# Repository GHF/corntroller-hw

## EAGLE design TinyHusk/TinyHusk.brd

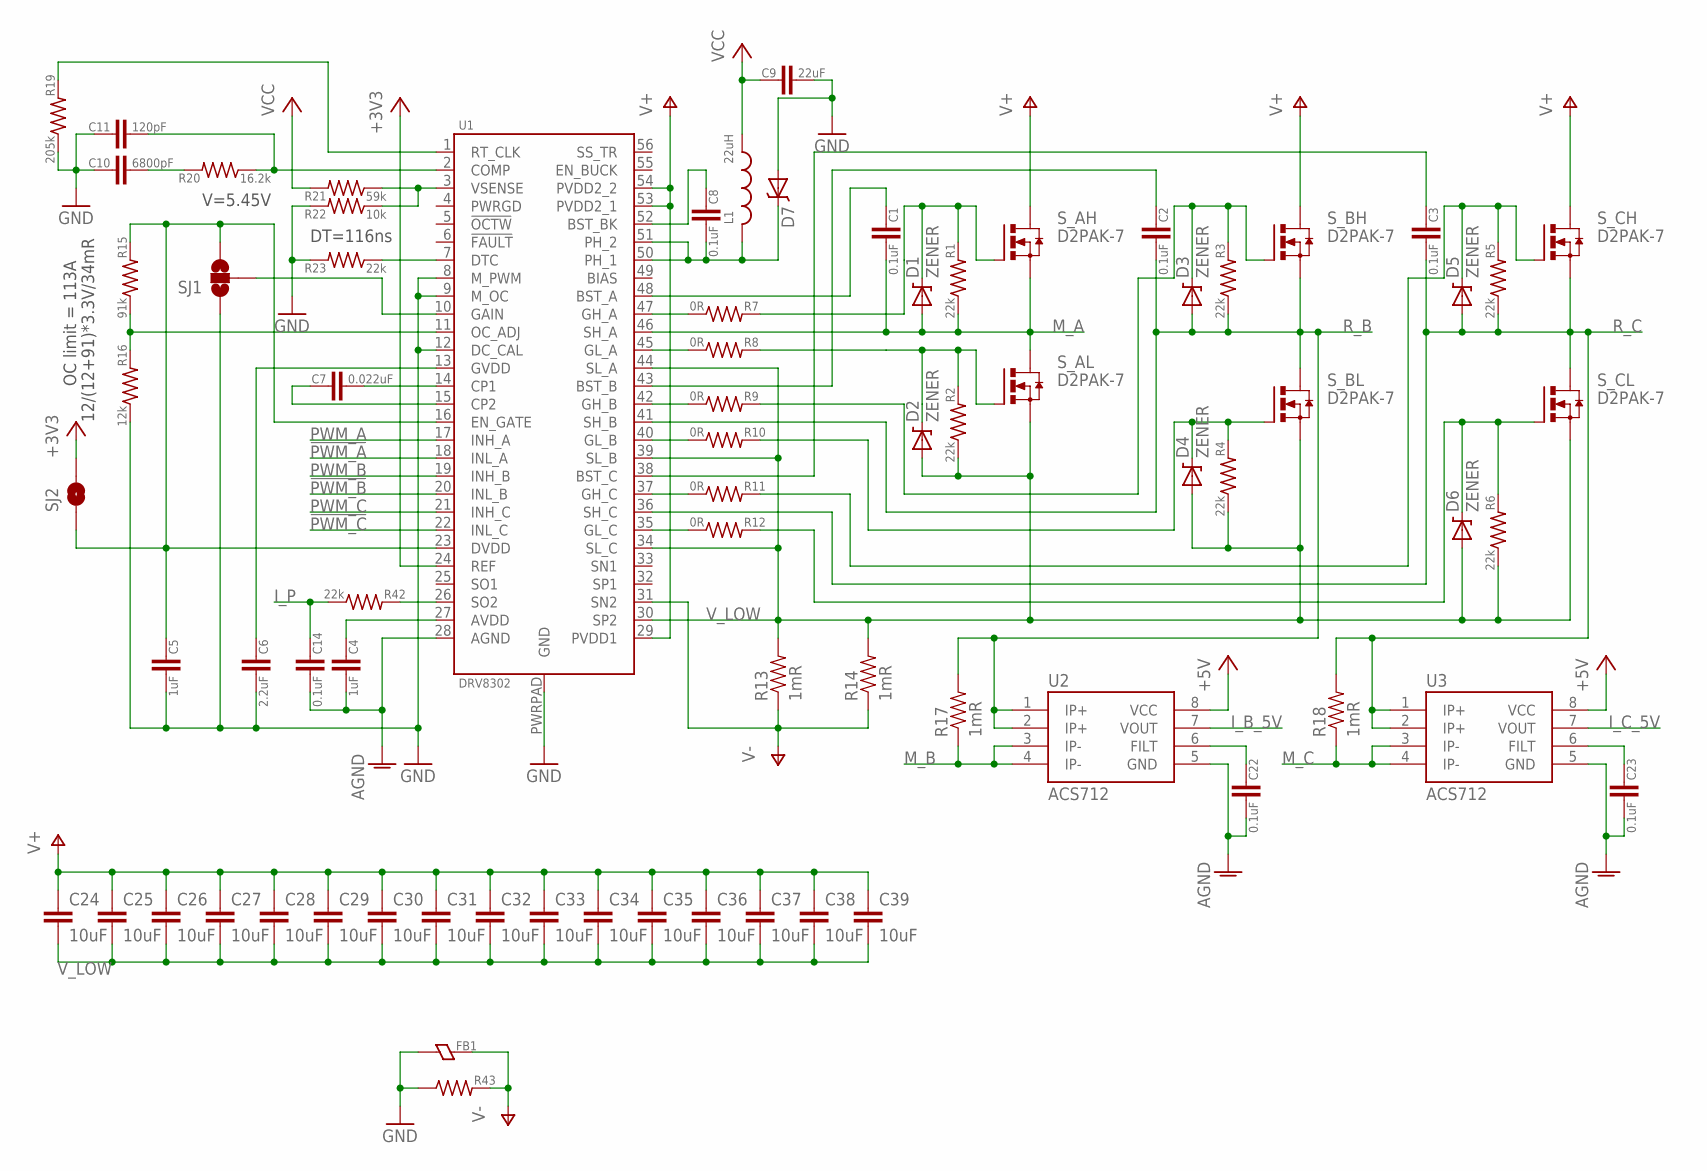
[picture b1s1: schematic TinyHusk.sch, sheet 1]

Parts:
C1, C2, C3, C8, C14, C22, C23: 0.1uF; 0603
C4, C5: 1uF; 0603
C6: 2.2uF; 0603
C7: 0.022uF; 0603
C9: 22uF; 0805
C10: 6800pF; 0603
C11: 120pF; 0603
C24, C25, C26, C27, C28, C29, C30, C31, C32, C33, C34, C35, C36, C37, C38, C39: 10uF; 1210
D1, D2, D3, D4, D5, D6: ZENER; SOD-323
D7: DIODE-SCHOTTKY_; SMA-DIODE
FB1: FERRITE0603; 0603
L1: 22uH; TAIYO-YUDEN_NR50
R1, R2, R3, R4, R5, R6, R23, R42: 22k; 0603
R7, R8, R9, R10, R11, R12: 0R; 0603
R13, R14, R17, R18: 1mR; R2512
R15: 91k; 0603
R16: 12k; 0603
R19: 205k; 0603
R20: 16.2k; 0603
R21: 59k; 0603
R22: 10k; 0603
R43: R0603; 0603
SJ1: SOLDERJUMPER_2WAYS; SJ_X
SJ2: SOLDERJUMPERTRACE; SJ_2S-TRACE
S_AH: D2PAK-7
S_AL: D2PAK-7
S_BH: D2PAK-7
S_BL: D2PAK-7
S_CH: D2PAK-7
S_CL: D2PAK-7
U1: DRV8302; HTSSOP-56
U2, U3: ACS712; SO08

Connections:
!PWM_A: U1.18 (INL_A); also elsewhere on the board
!PWM_B: U1.20 (INL_B); also elsewhere on the board
!PWM_C: U1.22 (INL_C); also elsewhere on the board
+3V3: SJ2.2, U1.24 (REF); also elsewhere on the board
+5V: U2.8 (VCC), U3.8 (VCC); also elsewhere on the board
AGND: C4.2, C14.2, C22.2, C23.2, U1.28 (AGND), U2.5 (GND), U3.5 (GND); also elsewhere on the board
GND: C5.2, C6.2, C9.2, C10.1, C11.1, D7.A, FB1.1, R16.1, R19.1, R22.2, R23.2, R43.1, SJ1.1, U1.8 (M_PWM), U1.9 (M_OC), U1.12 (DC_CAL), U1.PWRPAD (GND); also elsewhere on the board
I_B_5V: U2.7 (VOUT); also elsewhere on the board
I_C_5V: U3.7 (VOUT); also elsewhere on the board
I_P: C14.1, R42.1; also elsewhere on the board
M_A: C1.2, D1.2 (A), R1.1, S_AH.2 (S), S_AH.3 (S), S_AH.5 (S), S_AH.6 (S), S_AH.7 (S), S_AL.4 (D), U1.46 (SH_A); also elsewhere on the board
M_B: R17.1, U2.3 (IP-), U2.4 (IP-)
M_C: R18.1, U3.3 (IP-), U3.4 (IP-)
unnamed: R7.1, U1.47 (GH_A)
unnamed: R8.1, U1.45 (GL_A)
unnamed: R42.2, U1.26 (SO2)
unnamed: D1.1 (C), R1.2, R7.2, S_AH.1 (G)
unnamed: D3.1 (C), R3.2, R9.2, S_BH.1 (G)
unnamed: C22.1, U2.6 (FILT)
unnamed: D4.1 (C), R4.2, R10.2, S_BL.1 (G)
unnamed: R21.1, R22.1, U1.3 (VSENSE)
unnamed: D5.1 (C), R5.2, R11.2, S_CH.1 (G)
unnamed: C23.1, U3.6 (FILT)
unnamed: D6.1 (C), R6.2, R12.2, S_CL.1 (G)
unnamed: R9.1, U1.42 (GH_B)
unnamed: C1.1, U1.48 (BST_A)
unnamed: C2.1, U1.43 (BST_B)
unnamed: C3.1, U1.38 (BST_C)
unnamed: R10.1, U1.40 (GL_B)
unnamed: R11.1, U1.37 (GH_C)
unnamed: D2.1 (C), R2.2, R8.2, S_AL.1 (G)
unnamed: R12.1, U1.35 (GL_C)
unnamed: SJ1.2, U1.10 (GAIN)
unnamed: C5.1, R15.2, SJ1.3, SJ2.1, U1.16 (EN_GATE), U1.23 (DVDD)
unnamed: C4.1, U1.27 (AVDD)
unnamed: C6.1, U1.13 (GVDD)
unnamed: C7.2, U1.14 (CP1)
unnamed: C7.1, U1.15 (CP2)
unnamed: R15.1, R16.2, U1.11 (OC_ADJ)
unnamed: C8.2, D7.C, L1.P$2 (2), U1.50 (PH_1), U1.51 (PH_2)
unnamed: C8.1, U1.52 (BST_BK)
unnamed: C11.2, R20.1, U1.2 (COMP)
unnamed: C10.2, R20.2
unnamed: R19.2, U1.1 (RT_CLK)
unnamed: R23.1, U1.7 (DTC)
PWM_A: U1.17 (INH_A); also elsewhere on the board
PWM_B: U1.19 (INH_B); also elsewhere on the board
PWM_C: U1.21 (INH_C); also elsewhere on the board
R_B: C2.2, D3.2 (A), R3.1, R17.2, S_BH.2 (S), S_BH.3 (S), S_BH.5 (S), S_BH.6 (S), S_BH.7 (S), S_BL.4 (D), U1.41 (SH_B), U2.1 (IP+), U2.2 (IP+); also elsewhere on the board
R_C: C3.2, D5.2 (A), R5.1, R18.2, S_CH.2 (S), S_CH.3 (S), S_CH.5 (S), S_CH.6 (S), S_CH.7 (S), S_CL.4 (D), U1.36 (SH_C), U3.1 (IP+), U3.2 (IP+); also elsewhere on the board
V+: C24.1, C25.1, C26.1, C27.1, C28.1, C29.1, C30.1, C31.1, C32.1, C33.1, C34.1, C35.1, C36.1, C37.1, C38.1, C39.1, S_AH.4 (D), S_BH.4 (D), S_CH.4 (D), U1.29 (PVDD1), U1.53 (PVDD2_1), U1.54 (PVDD2_2); also elsewhere on the board
V-: FB1.2, R13.1, R14.1, R43.2, U1.31 (SN2); also elsewhere on the board
VCC: C9.1, L1.P$1 (1), R21.2; also elsewhere on the board
V_LOW: C24.2, C25.2, C26.2, C27.2, C28.2, C29.2, C30.2, C31.2, C32.2, C33.2, C34.2, C35.2, C36.2, C37.2, C38.2, C39.2, D2.2 (A), D4.2 (A), D6.2 (A), R2.1, R4.1, R6.1, R13.2, R14.2, S_AL.2 (S), S_AL.3 (S), S_AL.5 (S), S_AL.6 (S), S_AL.7 (S), S_BL.2 (S), S_BL.3 (S), S_BL.5 (S), S_BL.6 (S), S_BL.7 (S), S_CL.2 (S), S_CL.3 (S), S_CL.5 (S), S_CL.6 (S), S_CL.7 (S), U1.30 (SP2), U1.34 (SL_C), U1.39 (SL_B), U1.44 (SL_A)

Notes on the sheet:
OC limit = 113A
12/(12+91)*3.3V/34mR
V=5.45V
DT=116ns

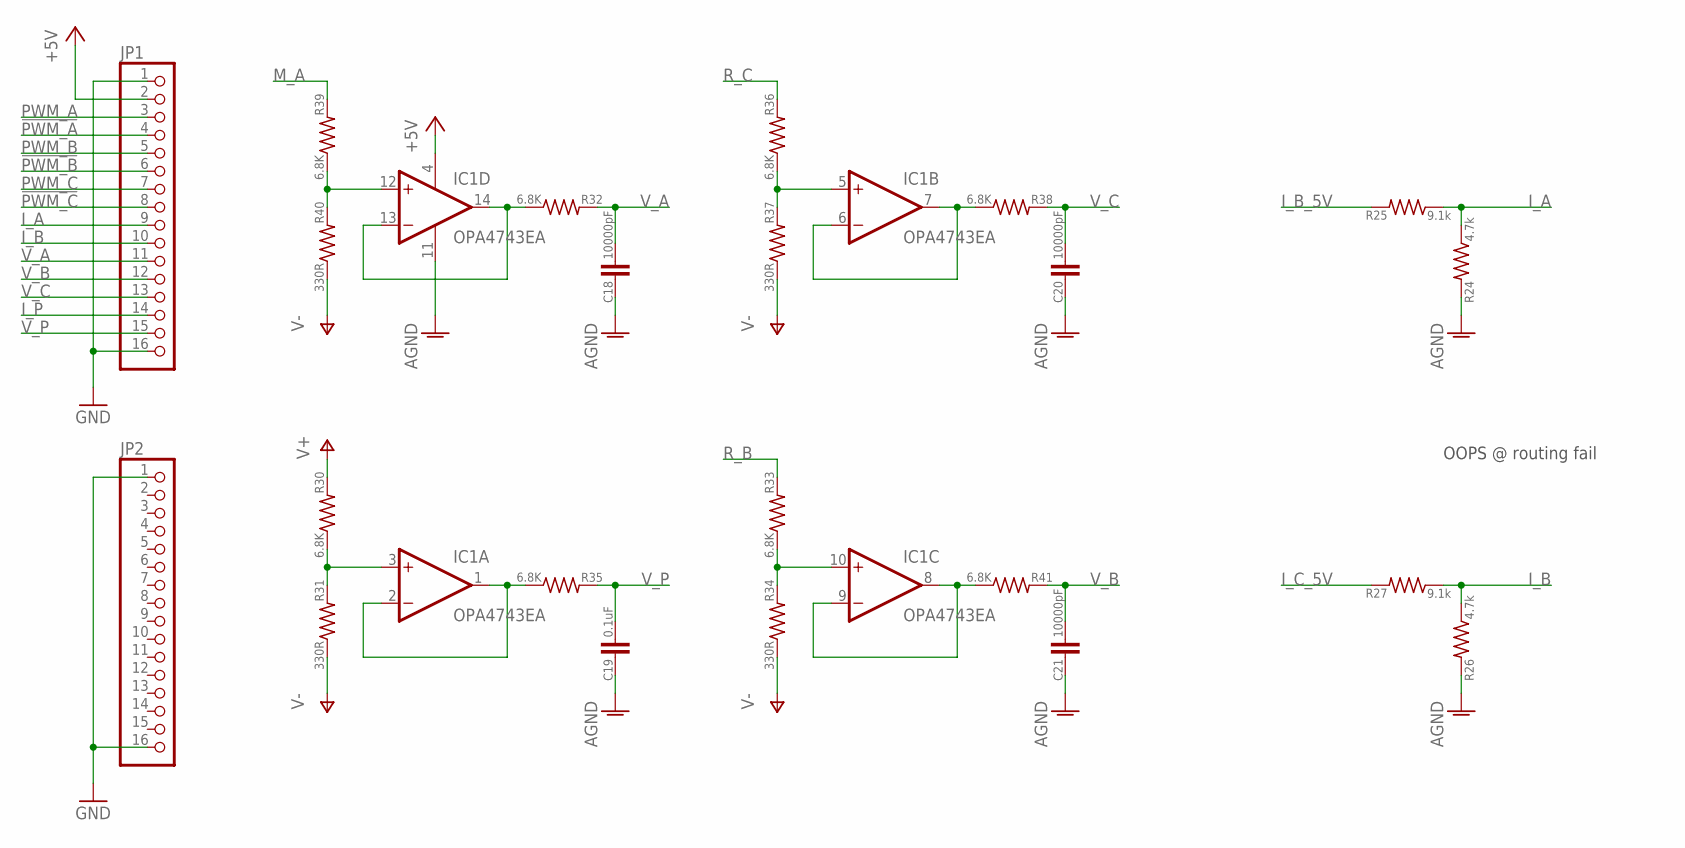
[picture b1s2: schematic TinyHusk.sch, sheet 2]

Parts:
C18, C20, C21: 10000pF; 0603
C19: 0.1uF; 0603
IC1: OPA4743EA; TSSOP14
JP1, JP2: PINHD-1X16_2.54-S; 1X16-S
R24, R26: 4.7k; 0603
R25, R27: 9.1k; 0603
R30, R32, R33, R35, R36, R38, R39, R41: 6.8K; 0603
R31, R34, R37, R40: 330R; 0603

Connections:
!PWM_A: JP1.4; also elsewhere on the board
!PWM_B: JP1.6; also elsewhere on the board
!PWM_C: JP1.8; also elsewhere on the board
+5V: IC1.4 (V+), JP1.2; also elsewhere on the board
AGND: C18.1, C19.1, C20.1, C21.1, IC1.11 (V-), R24.2, R26.2; also elsewhere on the board
GND: JP1.1, JP1.16, JP2.1, JP2.16; also elsewhere on the board
I_A: JP1.9, R24.1, R25.1
I_B: JP1.10, R26.1, R27.1
I_B_5V: R25.2; also elsewhere on the board
I_C_5V: R27.2; also elsewhere on the board
I_P: JP1.14; also elsewhere on the board
M_A: R39.2; also elsewhere on the board
unnamed: IC1.1 (OUT), IC1.2 (-IN), R35.1
unnamed: IC1.6 (-IN), IC1.7 (OUT), R38.1
unnamed: IC1.8 (OUT), IC1.9 (-IN), R41.1
unnamed: IC1.13 (-IN), IC1.14 (OUT), R32.1
unnamed: IC1.3 (+IN), R30.1, R31.2
unnamed: IC1.10 (+IN), R33.1, R34.2
unnamed: IC1.5 (+IN), R36.1, R37.2
unnamed: IC1.12 (+IN), R39.1, R40.2
PWM_A: JP1.3; also elsewhere on the board
PWM_B: JP1.5; also elsewhere on the board
PWM_C: JP1.7; also elsewhere on the board
R_B: R33.2; also elsewhere on the board
R_C: R36.2; also elsewhere on the board
V+: R30.2; also elsewhere on the board
V-: R31.1, R34.1, R37.1, R40.1; also elsewhere on the board
V_A: C18.2, JP1.11, R32.2
V_B: C21.2, JP1.12, R41.2
V_C: C20.2, JP1.13, R38.2
V_P: C19.2, JP1.15, R35.2

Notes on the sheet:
OOPS @ routing fail

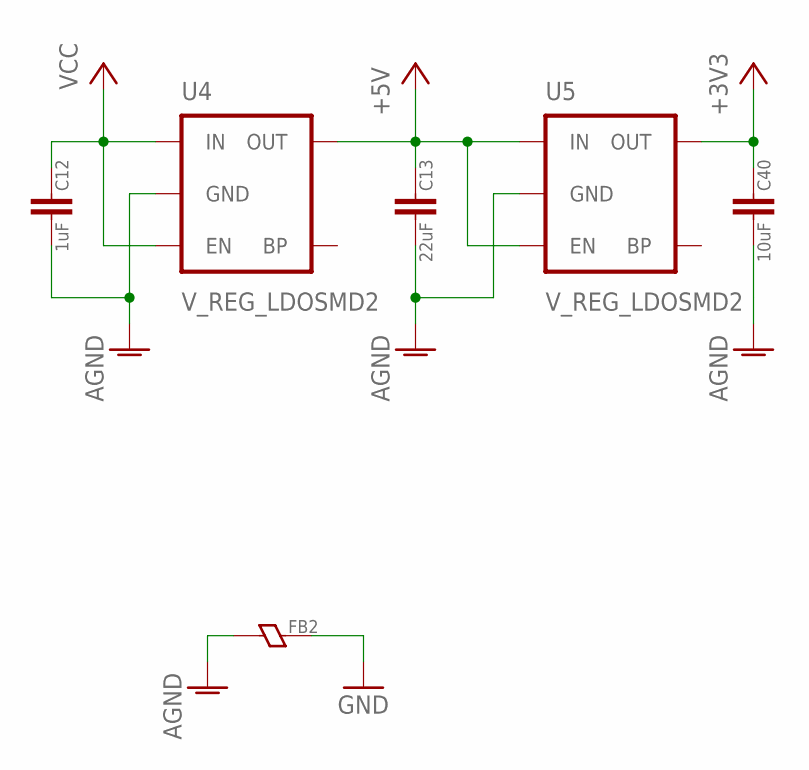
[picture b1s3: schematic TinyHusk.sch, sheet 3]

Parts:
C12: 1uF; 0603
C13: 22uF; 0805
C40: 10uF; 0603
FB2: FERRITE0603; 0603
U4, U5: V_REG_LDOSMD2; SC70

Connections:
+3V3: C40.1, U5.5 (OUT); also elsewhere on the board
+5V: C13.1, U4.5 (OUT), U5.1 (IN), U5.3 (EN); also elsewhere on the board
AGND: C12.2, C13.2, C40.2, FB2.1, U4.2 (GND), U5.2 (GND); also elsewhere on the board
GND: FB2.2; also elsewhere on the board
VCC: C12.1, U4.1 (IN), U4.3 (EN); also elsewhere on the board

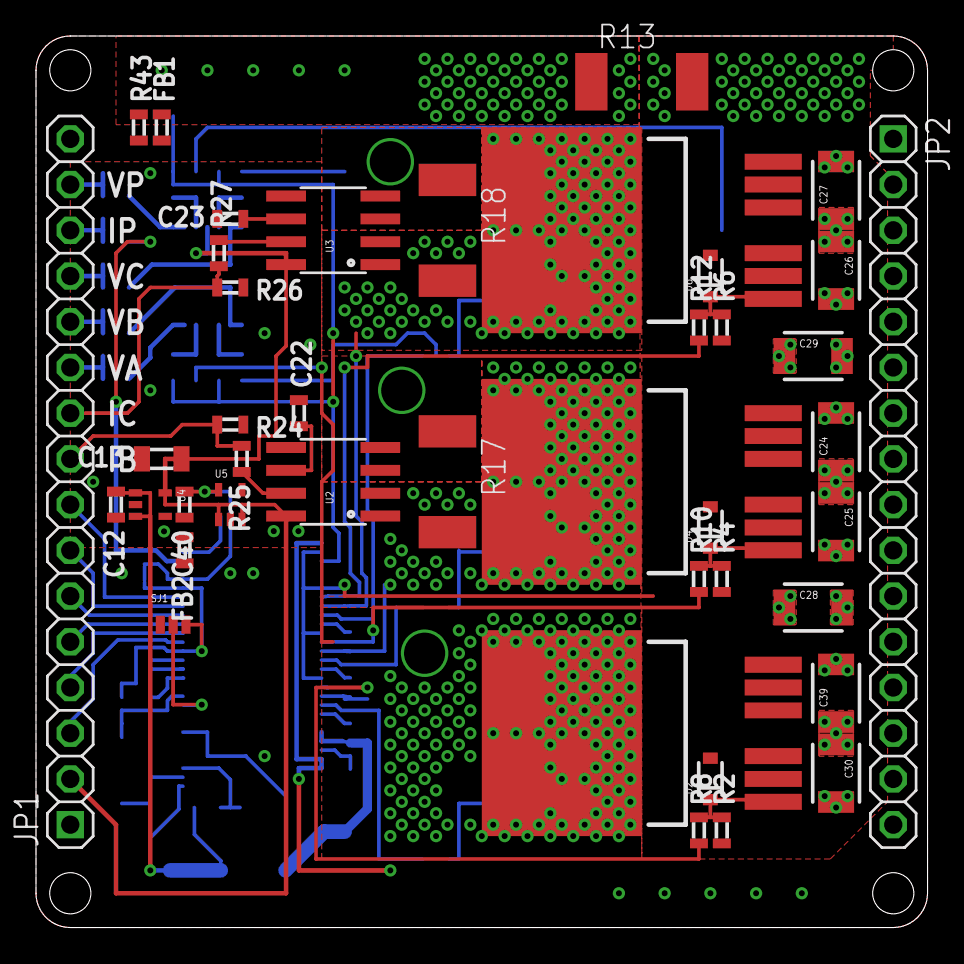
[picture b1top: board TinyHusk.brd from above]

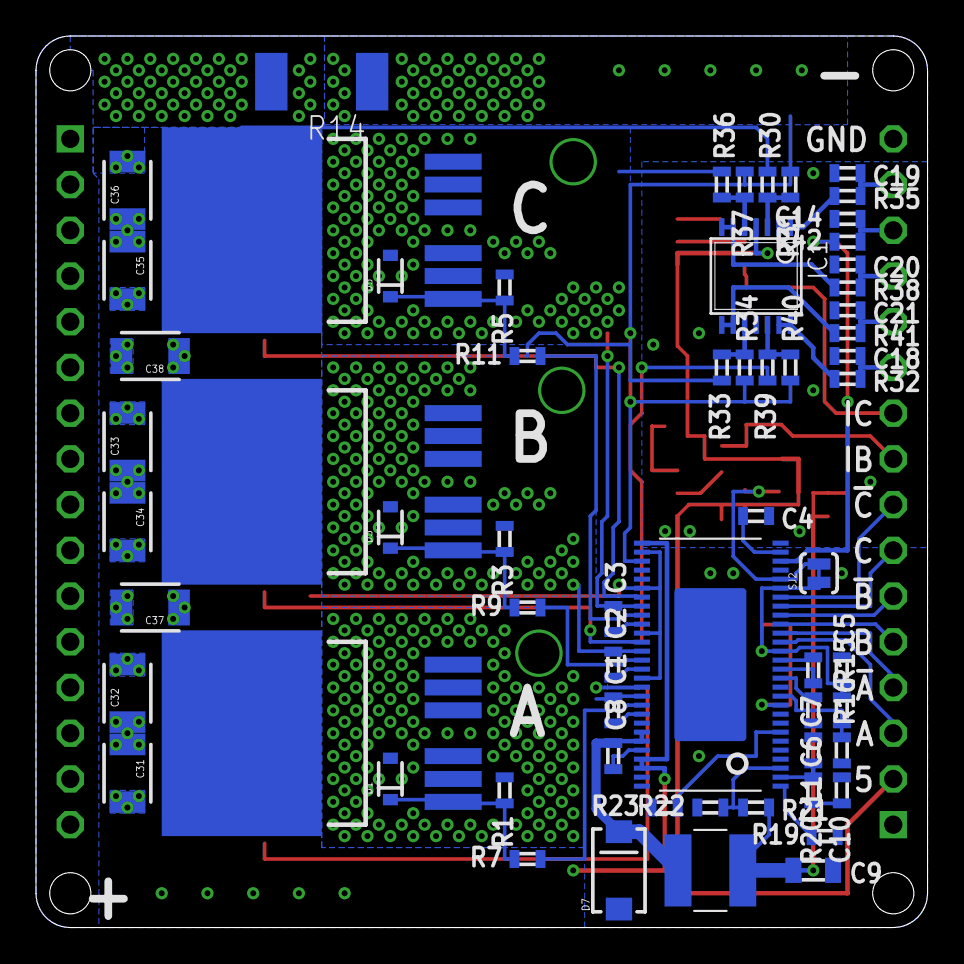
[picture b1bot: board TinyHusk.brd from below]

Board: 2 copper layers, 49.5 x 49.5 mm, 104 parts (62 on the bottom side), 68 nets.

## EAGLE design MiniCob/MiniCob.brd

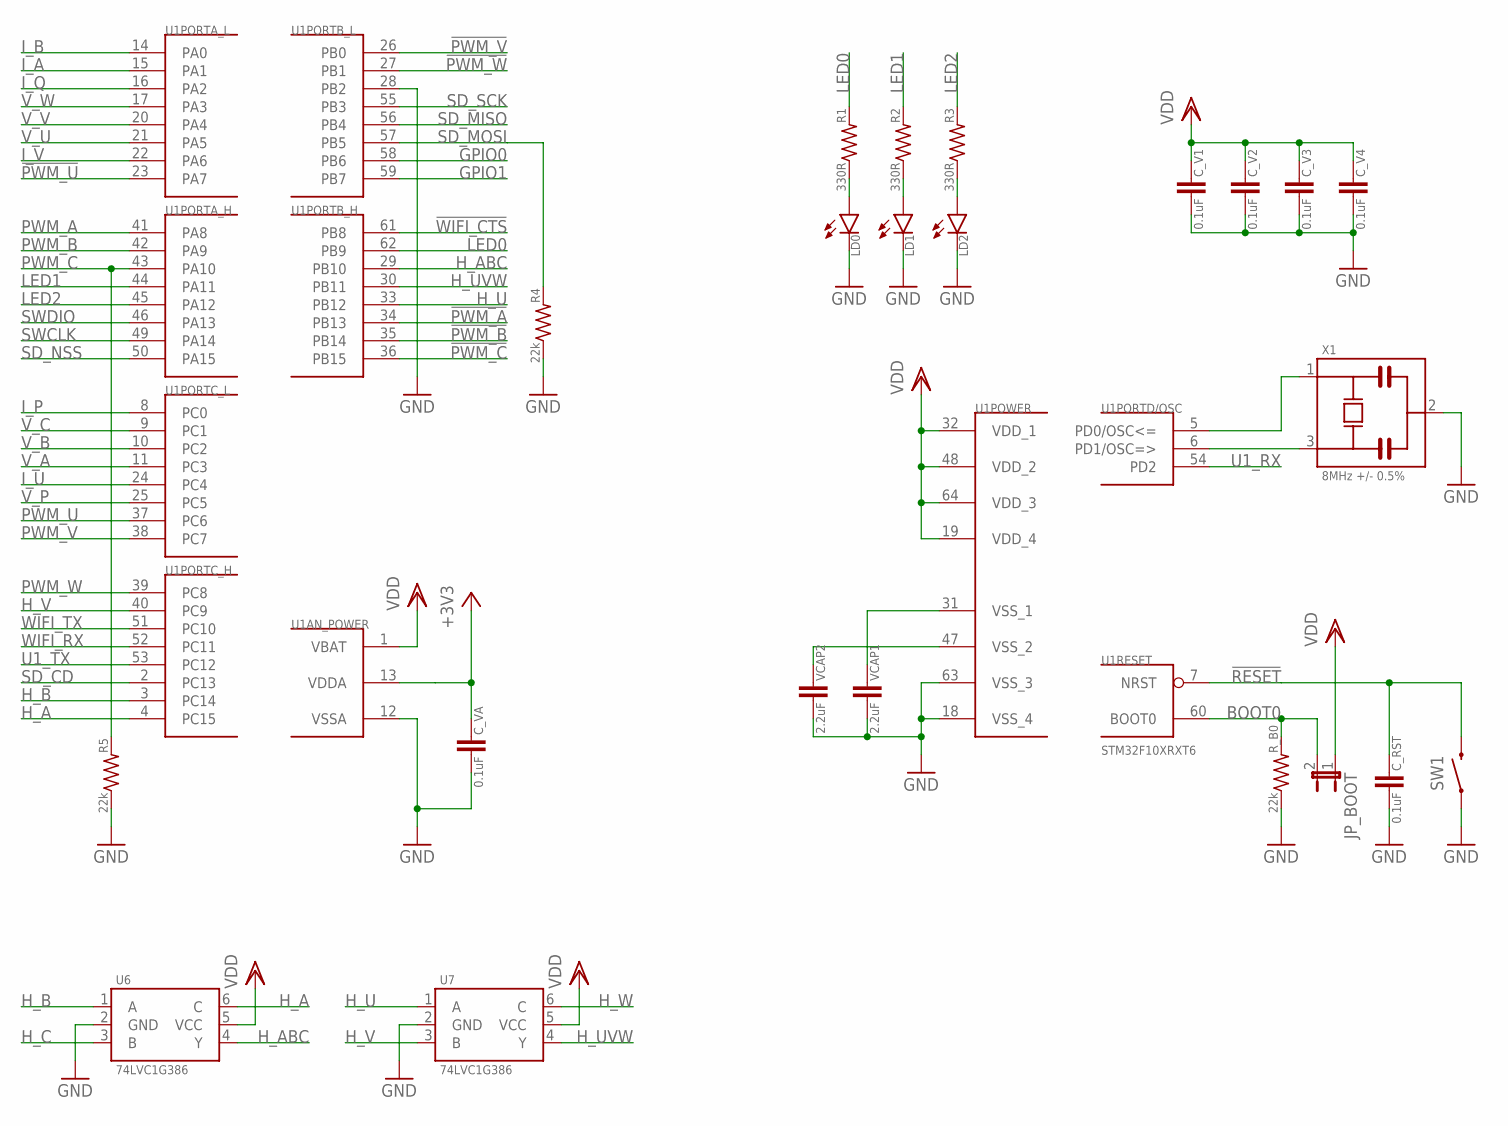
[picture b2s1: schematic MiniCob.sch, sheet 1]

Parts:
C_RST: 0.1uF; 0603
C_V1, C_V2, C_V3, C_V4: 0.1uF; 0603
C_VA: 0.1uF; 0603
JP_BOOT: JUMPER-2PTH; 1X02
LD0, LD1, LD2: LED0805; 0805_POL
R1, R2, R3: 330R; 0603
R4, R5: 22k; 0603
R_B0: 22k; 0603
SW1: SWITCH_SPST-NO; B3U-1000P
U1: STM32F10XRXT6; TQFP64
U6, U7: 74LVC1G386; SC-70
VCAP1, VCAP2: 2.2uF; 0603
X1: 8MHz +/- 0.5%; MURATA_CSTCE

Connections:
!PWM_A: U1.34 (PB13); also elsewhere on the board
!PWM_B: U1.35 (PB14); also elsewhere on the board
!PWM_C: U1.36 (PB15); also elsewhere on the board
!PWM_U: U1.23 (PA7); also elsewhere on the board
!PWM_V: U1.26 (PB0); also elsewhere on the board
!PWM_W: U1.27 (PB1); also elsewhere on the board
!RESET: C_RST.1, SW1.2, U1.7 (NRST); also elsewhere on the board
!WIFI_CTS: U1.61 (PB8); also elsewhere on the board
+3V3: C_VA.1, U1.13 (VDDA); also elsewhere on the board
BOOT0: JP_BOOT.2, R_B0.2, U1.60 (BOOT0)
GND: C_RST.2, C_V1.2, C_V2.2, C_V3.2, C_V4.2, C_VA.2, LD0.- (C), LD1.- (C), LD2.- (C), R4.1, R5.1, R_B0.1, SW1.1, U1.12 (VSSA), U1.18 (VSS_4), U1.28 (PB2), U1.63 (VSS_3), U6.2 (GND), U7.2 (GND), VCAP1.2, VCAP2.2, X1.2; also elsewhere on the board
GPIO0: U1.58 (PB6); also elsewhere on the board
GPIO1: U1.59 (PB7); also elsewhere on the board
H_A: U1.4 (PC15), U6.6 (C); also elsewhere on the board
H_ABC: U1.29 (PB10), U6.4 (Y)
H_B: U1.3 (PC14), U6.1 (A); also elsewhere on the board
H_C: U6.3 (B); also elsewhere on the board
H_U: U1.33 (PB12), U7.1 (A); also elsewhere on the board
H_UVW: U1.30 (PB11), U7.4 (Y)
H_V: U1.40 (PC9), U7.3 (B); also elsewhere on the board
H_W: U7.6 (C); also elsewhere on the board
I_A: U1.15 (PA1); also elsewhere on the board
I_B: U1.14 (PA0); also elsewhere on the board
I_P: U1.8 (PC0); also elsewhere on the board
I_Q: U1.16 (PA2); also elsewhere on the board
I_U: U1.24 (PC4); also elsewhere on the board
I_V: U1.22 (PA6); also elsewhere on the board
LED0: R1.2, U1.62 (PB9)
LED1: R2.2, U1.44 (PA11)
LED2: R3.2, U1.45 (PA12)
unnamed: U1.6 (PD1/OSC=>), X1.3
unnamed: U1.5 (PD0/OSC<=), X1.1
unnamed: U1.47 (VSS_2), VCAP2.1
unnamed: U1.31 (VSS_1), VCAP1.1
unnamed: LD0.+ (A), R1.1
unnamed: LD1.+ (A), R2.1
unnamed: LD2.+ (A), R3.1
PWM_A: U1.41 (PA8); also elsewhere on the board
PWM_B: U1.42 (PA9); also elsewhere on the board
PWM_C: R5.2, U1.43 (PA10); also elsewhere on the board
PWM_U: U1.37 (PC6); also elsewhere on the board
PWM_V: U1.38 (PC7); also elsewhere on the board
PWM_W: U1.39 (PC8); also elsewhere on the board
SD_CD: U1.2 (PC13); also elsewhere on the board
SD_MISO: U1.56 (PB4); also elsewhere on the board
SD_MOSI: R4.2, U1.57 (PB5); also elsewhere on the board
SD_NSS: U1.50 (PA15); also elsewhere on the board
SD_SCK: U1.55 (PB3); also elsewhere on the board
SWCLK: U1.49 (PA14); also elsewhere on the board
SWDIO: U1.46 (PA13); also elsewhere on the board
U1_RX: U1.54 (PD2); also elsewhere on the board
U1_TX: U1.53 (PC12); also elsewhere on the board
VDD: C_V1.1, C_V2.1, C_V3.1, C_V4.1, JP_BOOT.1, U1.1 (VBAT), U1.19 (VDD_4), U1.32 (VDD_1), U1.48 (VDD_2), U1.64 (VDD_3), U6.5 (VCC), U7.5 (VCC); also elsewhere on the board
V_A: U1.11 (PC3); also elsewhere on the board
V_B: U1.10 (PC2); also elsewhere on the board
V_C: U1.9 (PC1); also elsewhere on the board
V_P: U1.25 (PC5); also elsewhere on the board
V_U: U1.21 (PA5); also elsewhere on the board
V_V: U1.20 (PA4); also elsewhere on the board
V_W: U1.17 (PA3); also elsewhere on the board
WIFI_RX: U1.52 (PC11); also elsewhere on the board
WIFI_TX: U1.51 (PC10); also elsewhere on the board

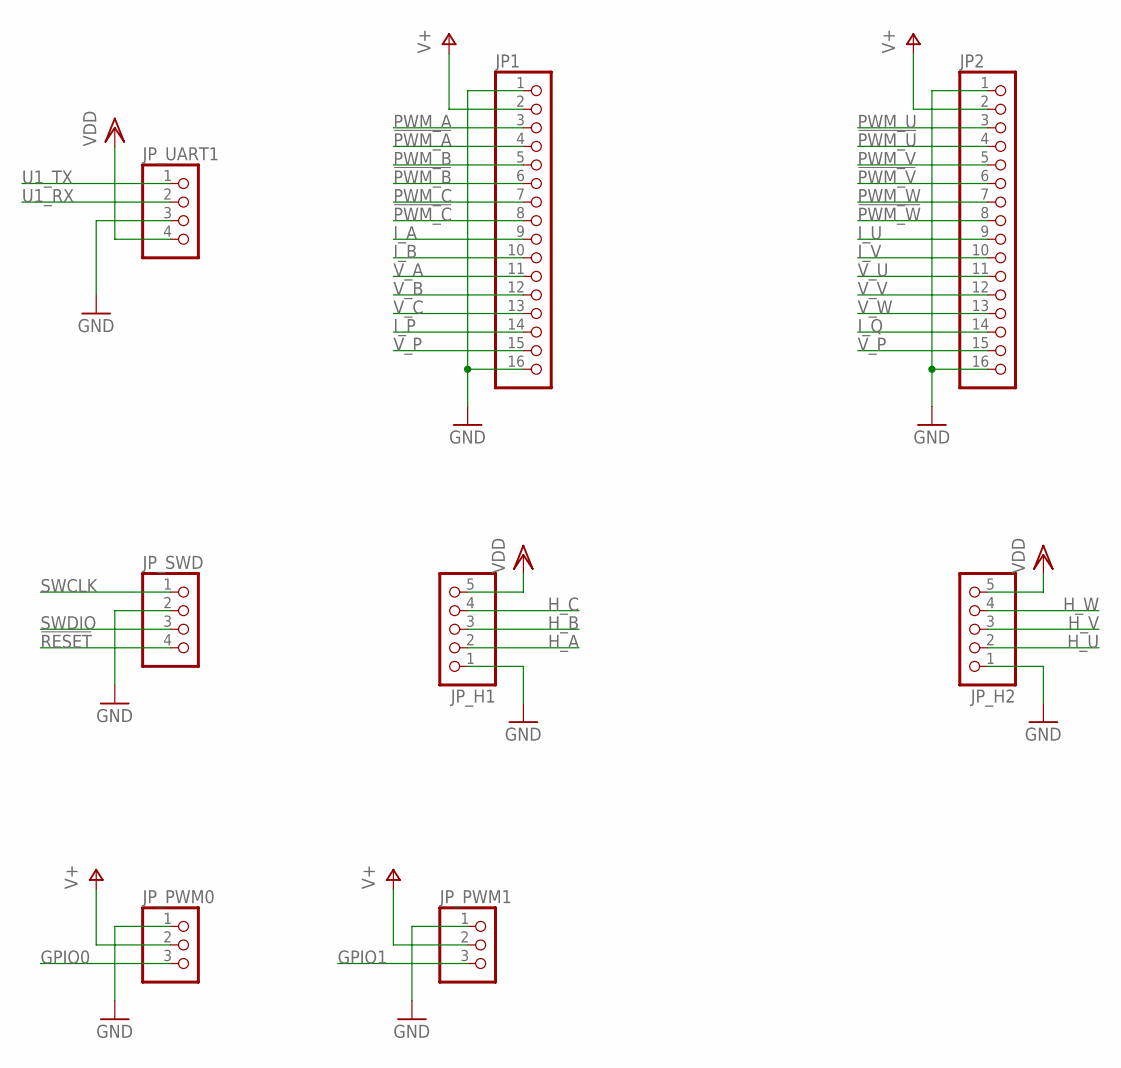
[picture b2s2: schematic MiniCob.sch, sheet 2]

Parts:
JP1, JP2: PINHD-1X16_2.54-S; 1X16-S
JP_H1, JP_H2: PINHD-1X05_2.54-S; 1X05-S
JP_PWM0, JP_PWM1: PINHD-1X03_2.54-S; 1X03-S
JP_SWD: PINHD-1X04_2.54-S; 1X04-S
JP_UART1: PINHD-1X04_2.54-S; 1X04-S

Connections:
!PWM_A: JP1.4; also elsewhere on the board
!PWM_B: JP1.6; also elsewhere on the board
!PWM_C: JP1.8; also elsewhere on the board
!PWM_U: JP2.4; also elsewhere on the board
!PWM_V: JP2.6; also elsewhere on the board
!PWM_W: JP2.8; also elsewhere on the board
!RESET: JP_SWD.4; also elsewhere on the board
GND: JP1.1, JP1.16, JP2.1, JP2.16, JP_H1.1, JP_H2.1, JP_PWM0.1, JP_PWM1.1, JP_SWD.2, JP_UART1.3; also elsewhere on the board
GPIO0: JP_PWM0.3; also elsewhere on the board
GPIO1: JP_PWM1.3; also elsewhere on the board
H_A: JP_H1.2; also elsewhere on the board
H_B: JP_H1.3; also elsewhere on the board
H_C: JP_H1.4; also elsewhere on the board
H_U: JP_H2.2; also elsewhere on the board
H_V: JP_H2.3; also elsewhere on the board
H_W: JP_H2.4; also elsewhere on the board
I_A: JP1.9; also elsewhere on the board
I_B: JP1.10; also elsewhere on the board
I_P: JP1.14; also elsewhere on the board
I_Q: JP2.14; also elsewhere on the board
I_U: JP2.9; also elsewhere on the board
I_V: JP2.10; also elsewhere on the board
PWM_A: JP1.3; also elsewhere on the board
PWM_B: JP1.5; also elsewhere on the board
PWM_C: JP1.7; also elsewhere on the board
PWM_U: JP2.3; also elsewhere on the board
PWM_V: JP2.5; also elsewhere on the board
PWM_W: JP2.7; also elsewhere on the board
SWCLK: JP_SWD.1; also elsewhere on the board
SWDIO: JP_SWD.3; also elsewhere on the board
U1_RX: JP_UART1.2; also elsewhere on the board
U1_TX: JP_UART1.1; also elsewhere on the board
V+: JP1.2, JP2.2, JP_PWM0.2, JP_PWM1.2; also elsewhere on the board
VDD: JP_H1.5, JP_H2.5, JP_UART1.4; also elsewhere on the board
V_A: JP1.11; also elsewhere on the board
V_B: JP1.12; also elsewhere on the board
V_C: JP1.13; also elsewhere on the board
V_P: JP1.15, JP2.15; also elsewhere on the board
V_U: JP2.11; also elsewhere on the board
V_V: JP2.12; also elsewhere on the board
V_W: JP2.13; also elsewhere on the board

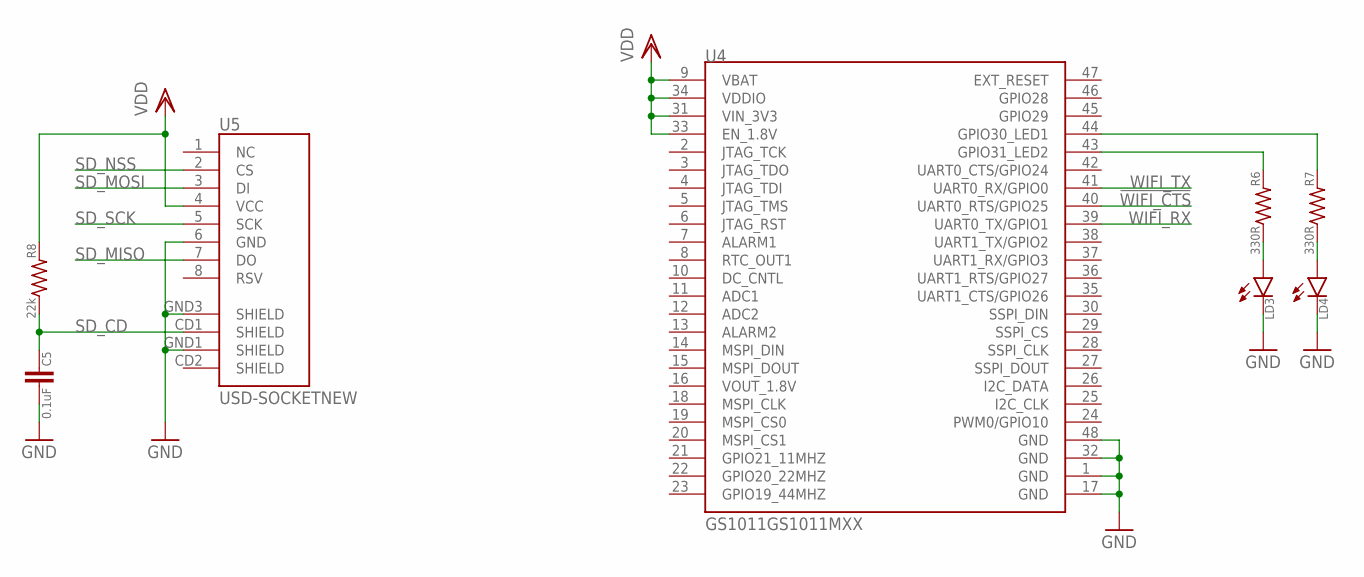
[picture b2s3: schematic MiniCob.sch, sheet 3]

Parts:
C5: 0.1uF; 0603
LD3, LD4: LED0805; 0805_POL
R6, R7: 330R; 0603
R8: 22k; 0603
U4: GS1011GS1011MXX; GS1011MXX
U5: USD-SOCKETNEW; MICRO-SD-SOCKET-PP

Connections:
!WIFI_CTS: U4.40 (UART0_RTS/GPIO25); also elsewhere on the board
GND: C5.2, LD3.- (C), LD4.- (C), U4.1 (GND), U4.17 (GND), U4.32 (GND), U4.48 (GND), U5.6 (GND), U5.GND1 (SHIELD), U5.GND3 (SHIELD); also elsewhere on the board
unnamed: R7.2, U4.44 (GPIO30_LED1)
unnamed: R6.2, U4.43 (GPIO31_LED2)
unnamed: LD3.+ (A), R6.1
unnamed: LD4.+ (A), R7.1
SD_CD: C5.1, R8.1, U5.CD1 (SHIELD); also elsewhere on the board
SD_MISO: U5.7 (DO); also elsewhere on the board
SD_MOSI: U5.3 (DI); also elsewhere on the board
SD_NSS: U5.2 (CS); also elsewhere on the board
SD_SCK: U5.5 (SCK); also elsewhere on the board
VDD: R8.2, U4.9 (VBAT), U4.31 (VIN_3V3), U4.33 (EN_1.8V), U4.34 (VDDIO), U5.4 (VCC); also elsewhere on the board
WIFI_RX: U4.39 (UART0_TX/GPIO1); also elsewhere on the board
WIFI_TX: U4.41 (UART0_RX/GPIO0); also elsewhere on the board

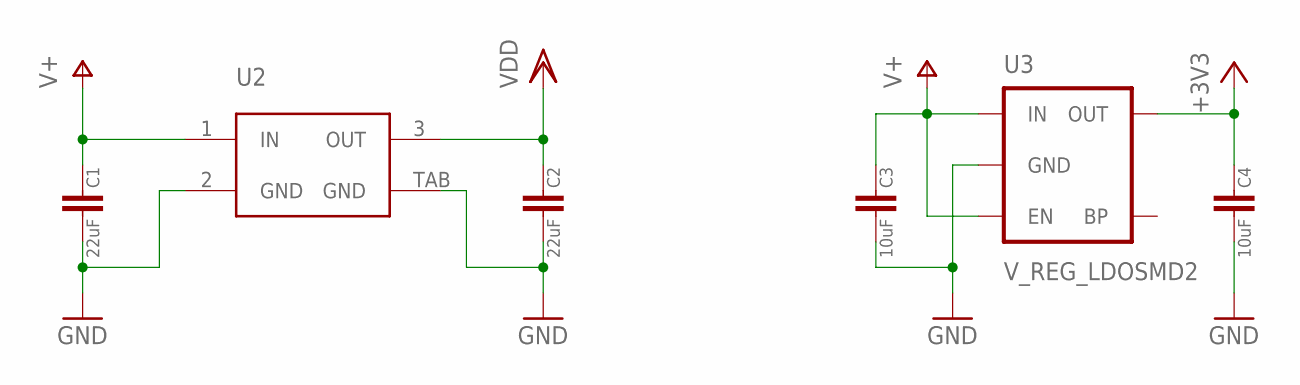
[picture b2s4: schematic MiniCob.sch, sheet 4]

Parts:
C1, C2: 22uF; 0805
C3, C4: 10uF; 0805
U2: MCP1826S; SOT223-3L
U3: V_REG_LDOSMD2; SC70

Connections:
+3V3: C4.1, U3.5 (OUT); also elsewhere on the board
GND: C1.2, C2.2, C3.2, C4.2, U2.2 (GND), U2.TAB (GND), U3.2 (GND); also elsewhere on the board
V+: C1.1, C3.1, U2.1 (IN), U3.1 (IN), U3.3 (EN); also elsewhere on the board
VDD: C2.1, U2.3 (OUT); also elsewhere on the board

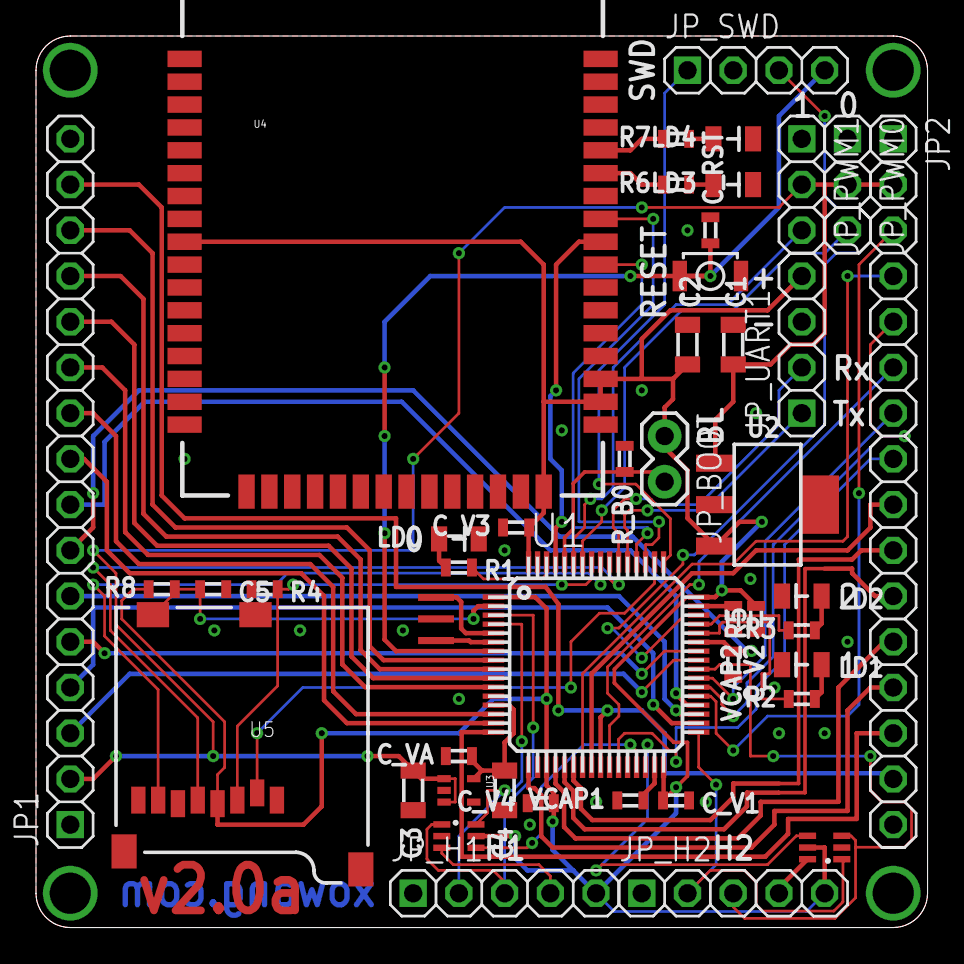
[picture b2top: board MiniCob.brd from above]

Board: 2 copper layers, 49.5 x 49.5 mm, 45 parts (0 on the bottom side), 67 nets.

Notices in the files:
parts and their libraries:
SparkFun: Licensing: CC v3.0 Share-Alike You are welcome to use this library for commercial purposes.
